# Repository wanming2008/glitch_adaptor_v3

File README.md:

# glitch_adaptor_v3

Voltage glitching driver board using LM5134 and IRF7607.

This is designed for use with the ChipWhisperer-Lite. For best performance, physically remove or disconnect the built-in glitching FETs on the CW-Lite board and connect the gate drive signal to this glitching board via coax. The connection from glitch board to target Vcore signal should be very short, I used about a centimeter of twisted heavy-gauge magnet wire. The FET drivers run from 12.5 volts to get the fastest slew rates we can. This circuit switches in a capacitor bank to stabilize Vcore when not glitching, intended for use with chips that have a low voltage core with a built-in regulator.

Board layout for KiCad, thrown together for quick assembly using the parts I had on hand. You may want to substitute your favorite voltage regulators if you like.

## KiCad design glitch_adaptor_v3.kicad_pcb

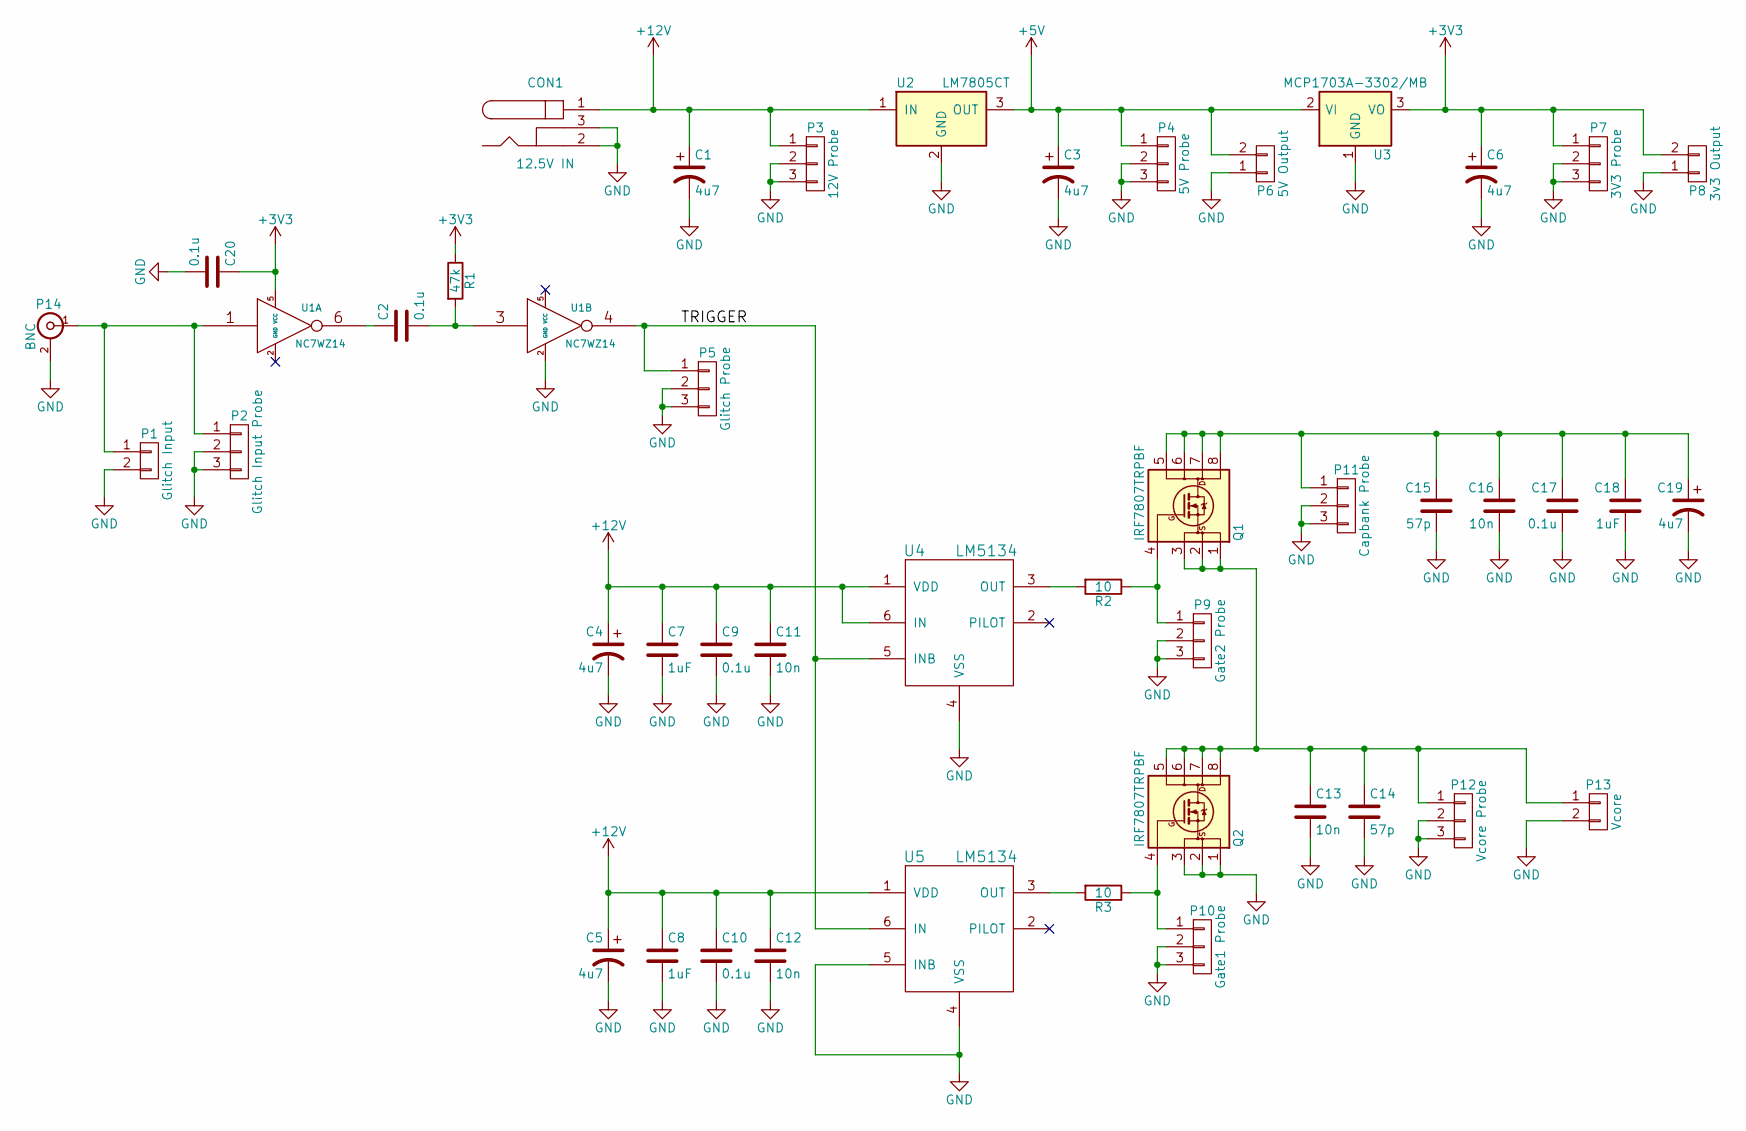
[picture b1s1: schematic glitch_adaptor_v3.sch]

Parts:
C1, C3, C4, C5, C6, C19: 4u7; C_1206_HandSoldering
C2, C9, C10, C17, C20: 0.1u; C_0805_HandSoldering
C7, C8, C18: 1uF; C_0805_HandSoldering
C11, C12, C13, C16: 10n; C_0805_HandSoldering
C14, C15: 57p; C_0805_HandSoldering
CON1: 12.5V IN; BARREL_JACK
P1: Glitch Input; Pin_Header_Straight_1x02
P2: Glitch Input Probe; ScopeProbe3pin
P3: 12V Probe; ScopeProbe3pin
P4: 5V Probe; ScopeProbe3pin
P5: Glitch Probe; ScopeProbe3pin
P6: 5V Output; Pin_Header_Straight_1x02
P7: 3V3 Probe; ScopeProbe3pin
P8: 3v3 Output; Pin_Header_Straight_1x02
P9: Gate2 Probe; ScopeProbe3pin
P10: Gate1 Probe; ScopeProbe3pin
P11: Capbank Probe; ScopeProbe3pin
P12: Vcore Probe; ScopeProbe3pin
P13: Vcore; Pin_Header_Straight_1x02
P14: BNC; SMB_Straight
Q1, Q2: IRF7807TRPBF; SOIC-8_3.9x4.9mm_Pitch1.27mm
R1: 47k; R_0805_HandSoldering
R2, R3: 10; R_0805_HandSoldering
U1: NC7WZ14; SC-70-6_Handsoldering
U2: LM7805CT; TO-220_Neutral123_Horizontal_LargePads
U3: MCP1703A-3302/MB; TO-92_Rugged
U4, U5: LM5134; SOT-23-6_Handsoldering

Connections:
+3V3: C6.1, C20.1, P7.1, P8.2, R1.1, U1.5 (VCC), U3.3 (VO)
+5V: C3.1, P4.1, P6.2, U2.3 (OUT), U3.2 (VI)
+12V: C1.1, C4.1, C5.1, C7.1, C8.1, C9.1, C10.1, C11.1, C12.1, CON1.1, P3.1, U2.1 (IN), U4.1 (VDD), U4.6 (IN), U5.1 (VDD)
/TRIGGER: P5.1, U1.4, U4.5 (INB), U5.6 (IN)
GND: C1.2, C3.2, C4.2, C5.2, C6.2, C7.2, C8.2, C9.2, C10.2, C11.2, C12.2, C13.2, C14.2, C15.2, C16.2, C17.2, C18.2, C19.2, C20.2, CON1.2, CON1.3, P1.2, P2.2, P2.3, P3.2, P3.3, P4.2, P4.3, P5.2, P5.3, P6.1, P7.2, P7.3, P8.1, P9.2, P9.3, P10.2, P10.3, P11.2, P11.3, P12.2, P12.3, P13.2, P14.2 (Ext), Q2.1 (S), Q2.2 (S), Q2.3 (S), U1.2 (GND), U2.2 (GND), U3.1 (GND), U4.4 (VSS), U5.4 (VSS), U5.5 (INB)
unnamed: C2.1, U1.6
unnamed: C2.2, R1.2, U1.3
unnamed: C13.1, C14.1, P12.1, P13.1, Q1.1 (S), Q1.2 (S), Q1.3 (S), Q2.5 (D), Q2.6 (D), Q2.7 (D), Q2.8 (D)
unnamed: C15.1, C16.1, C17.1, C18.1, C19.1, P11.1, Q1.5 (D), Q1.6 (D), Q1.7 (D), Q1.8 (D)
unnamed: P1.1, P2.1, P14.1 (In), U1.1
unnamed: P9.1, Q1.4 (G), R2.1
unnamed: P10.1, Q2.4 (G), R3.1
unnamed: R2.2, U4.3 (OUT)
unnamed: R3.2, U5.3 (OUT)

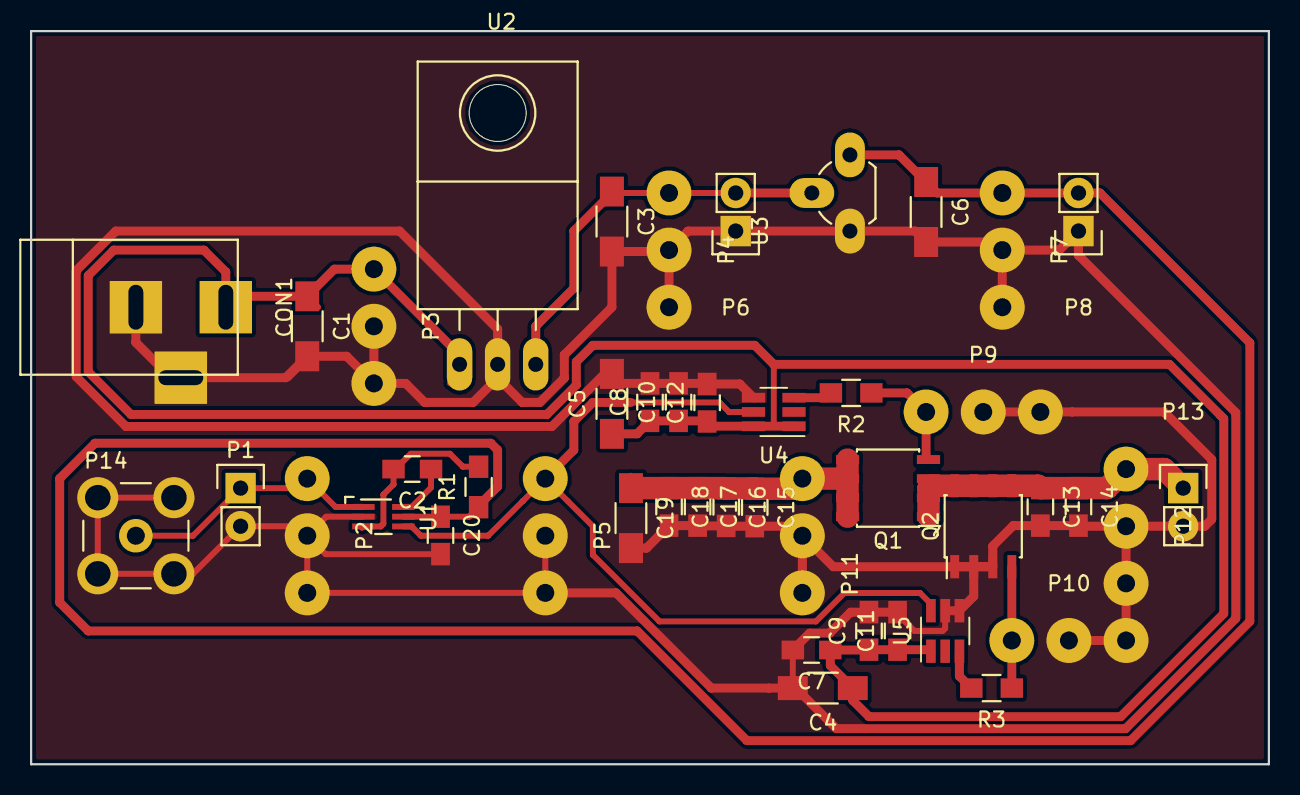
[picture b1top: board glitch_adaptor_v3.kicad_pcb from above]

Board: 2 copper layers, 82.6 x 48.9 mm, 45 parts (0 on the bottom side), 14 nets.

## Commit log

2017-07-20 Checkin
2017-08-24 for otherplan compatibility
